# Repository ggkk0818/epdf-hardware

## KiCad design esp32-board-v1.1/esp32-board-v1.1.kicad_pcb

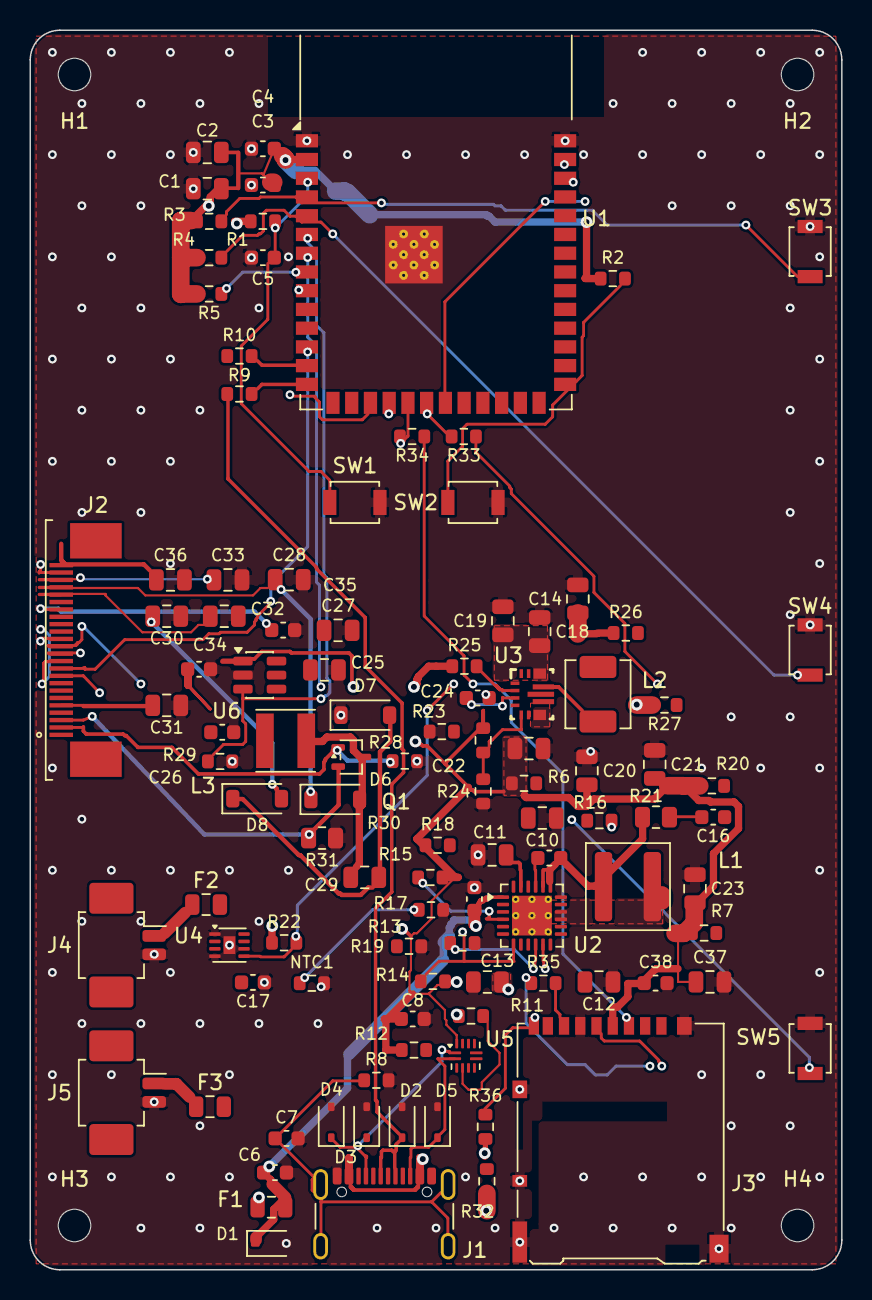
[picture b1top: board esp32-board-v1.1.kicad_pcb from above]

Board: 4 copper layers, 55.0 x 84.0 mm, 110 parts (0 on the bottom side), 70 nets.

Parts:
C1, C2, C10, C12, C13, C14, C15, C18, C19, C20, C21, C22, C23, C25, C27, C28, C29, C30, C31, C32, C33, C36, C37: C_0805_2012Metric
C3, C4, C5, C6, C7, C8, C9, C11, C16, C17, C24, C26, C34, C35, C38: C_0603_1608Metric
D1, D2, D3, D4, D5: D_SOD-323
D6, D7, D8: D_SOD-123
F1, F2, F3: Fuse_0805_2012Metric
H1, H2, H3, H4: MountingHole_2.2mm_M2
J1: USB_C_Receptacle_GCT_USB4105-xx-A_16P_TopMnt_Hori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; USB_C_Receptacle_GCT_USB4105-xx-A_16P_TopMnt_Horizontal
J2: X05B20U24T
J3: microSD_DM3AT-SF-PEJM5_EPDF
J4, J5: Molex_PicoBlade_53261-0271_1x02-1MP_P1.25mm_Horiz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; Molex_PicoBlade_53261-0271_1x02-1MP_P1.25mm_Horizontal
L1: L_Coilcraft_XAL5030-XXX
L2: L_Sunlord_MWSA0402S
L3: L_Taiyo-Yuden_NR-40xx
NTC1: R_0603_1608Metric
Q1: SOT-323_SC-70
R1, R2, R3, R4, R5, R6, R7, R8, R9, R10, R11, R12, R13, R14, R15, R16, R17, R18, R19, R20, R22, R23, R24, R25, R26, R27, R28, R29, R30, R32, R33, R34, R35, R36: R_0603_1608Metric
R21, R31: R_0805_2012Metric
SW1, SW2, SW3, SW4, SW5: SW_SPST_B3U-1000P
U1: ESP32-S3-WROOM-1_EPDF
U2: Texas_RTW_WQFN-24-1EP_4x4mm_P0.5mm_EP2.7x2.7mm_Th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; Texas_RTW_WQFN-24-1EP_4x4mm_P0.5mm_EP2.7x2.7mm_ThermalVias
U3: RNM0015A
U4: TDFN-8-1EP_2x2mm_P0.5mm_EP0.8x1.2mm
U5: Texas_X2QFN-12_1.6x1.6mm_P0.4mm
U6: SOT-23-6

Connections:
3V3_MAIN: C1.1, C2.1, C3.1, C4.1, C8.1, C20.1, C21.1, C22.1, C23.1, C37.1, C38.1, J3.4, R1.1, R2.1, R3.1, R4.1, R5.1, R6.1, R7.1, R12.1, R14.2, R15.2, R18.1, R20.1, R22.1, R23.1, R25.1, R32.1, R36.1, U1.2, U3.7, U3.8, U5.12, U6.1
BAT1_RAW: F2.1, J4.1
BAT2_RAW: F3.1, J5.1
BAT_BUS: C12.1, C17.1, F2.2, F3.2, U2.13, U2.14, U4.2, U4.3
BOOT: R2.2, SW2.1, U1.27
CHG_BTST: C11.1, U2.21
CHG_CE: R18.2, U1.24, U2.9
CHG_DSEL: R20.2, U2.24
CHG_ILIM: R13.1, U2.10
CHG_INT_N: R14.1, U1.9, U2.7
CHG_OTG: R19.1, U2.8
CHG_PMID: C15.1, U2.23
CHG_REGN: C10.1, R16.1, U2.22
CHG_SNUB: C16.1, R21.2
CHG_STAT: R15.1, U2.4
CHG_SW: C11.2, L1.1, R21.1, U2.19, U2.20
CHG_TS: NTC1.1, R16.2, R17.1, U2.11
EPD_3V3: C25.1, C26.1, C27.1, C34.1, J2.15, J2.16, L3.1, U6.6
EPD_BUSY: J2.9, U1.7
EPD_CS_N: J2.12, U1.18
EPD_DC: J2.11, U1.17
EPD_GDR: J2.2, Q1.1, R30.1
EPD_PWR_EN: R29.1, U1.6, U6.3
EPD_RESE: J2.3, Q1.2, R31.1
EPD_RST_N: J2.10, U1.12
EPD_SW: C29.1, D6.2, L3.2, Q1.3
EPD_VCOM: C36.1, J2.24
EPD_VDD: C35.1, J2.18
EPD_VGH: C28.1, D6.1, J2.21
EPD_VGL: C30.1, D8.2, J2.23
EPD_VSH1: C32.1, J2.20
EPD_VSH2: C31.1, J2.5
EPD_VSL: C33.1, J2.22
EPD_X: C29.2, D7.2, D8.1
FG_ALRT_N: R22.2, U1.39, U4.5
GND: C1.2, C2.2, C3.2, C4.2, C5.2, C6.2, C7.2, C8.2, C9.2, C10.2, C12.2, C13.2, C14.2, C15.2, C16.2, C17.2, C18.2, C19.2, C20.2, C21.2, C22.2, C23.2, C24.2, C25.2, C26.2, C27.2, C28.2, C30.2, C31.2, C32.2, C33.2, C34.2, C35.2, C36.2, C37.2, C38.2, D1.2, D2.2, D3.2, D4.2, D5.2, D7.1, J1.A1, J1.A12, J1.B1, J1.B12, J2.8, J2.17, J3.6, J3.10, J3.SH, J4.2, J5.2, NTC1.2, R8.2, R13.2, R17.2, R19.2, R24.2, R28.1, R29.2, R30.2, R31.2, SW1.2, SW2.2, SW3.2, SW4.2, SW5.2, U1.1, U1.40, U1.41, U2.17, U2.18, U2.25, U3.4, U3.10, U4.1, U4.4, U4.6, U4.9, U5.3, U5.5, U5.10, U5.11, U6.2
I2C_SCL: R7.2, U1.23, U2.5, U4.7, U5.8
I2C_SDA: R6.2, U1.11, U2.6, U4.8, U5.7
KEY1_N: R3.2, SW3.1, U1.4
KEY2_N: R4.2, SW4.1, U1.5
KEY3_N: R5.2, SW5.1, U1.8
RESET_N: C5.1, R1.2, SW1.1, U1.3
SPI_MISO: R35.1, U1.21
SPI_MOSI: J2.14, R34.1, U1.19
SPI_SCLK: J2.13, R33.1, U1.20
SYS: C13.1, C14.1, C18.1, C19.1, L1.2, R26.1, R27.1, U2.15, U2.16, U3.12, U3.13
TF_CD_N: J3.9, R36.2, U1.38
TF_CS_N: J3.2, R32.2, U1.22
TF_MISO: J3.7, R35.2
TF_MOSI: J3.3, R34.2
TF_SCLK: J3.5, R33.2
TPS_EN: R26.2, U3.14
TPS_FB: R23.2, R24.1, U3.5
TPS_L1: L2.1, U3.11
TPS_L2: L2.2, U3.9
TPS_PG: R25.2, U3.2
TPS_PS_SYNC: R27.2, U3.1
TPS_VAUX: C24.1, U3.3
TPS_VSEL: R28.2, U3.15
TYPEC_INT_N: R12.2, U1.10, U5.6
USB_CC1: D4.1, J1.A5, U5.1
USB_CC2: D5.1, J1.B5, U5.2
USB_DN: R10.2, U1.13
USB_DN_CONN: D3.1, J1.A7, J1.B7, R10.1
USB_DP: R9.2, U1.14
USB_DP_CONN: D2.1, J1.A6, J1.B6, R9.1
USB_SHIELD: C7.1, J1.SH, R8.1
USB_VBUS_DET: R11.2, U5.4
USB_VBUS_PROT: C6.1, C9.1, D1.1, F1.2, U2.1
USB_VBUS_RAW: F1.1, J1.A4, J1.A9, J1.B4, J1.B9, R11.1

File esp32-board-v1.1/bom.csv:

"Reference","Value","Footprint","Status","MPN","Populate"
"C1,C13,C14,C21-C23","22uF","Capacitor_SMD:C_0805_2012Metric","RELEASED","TCC0805X5R226K250FT（华秋 G14559843）","FIT"
"C2,C12,C15,C18-C20,C25,C37","10uF","Capacitor_SMD:C_0805_2012Metric","RELEASED","CL21A106KAYNNNE（华秋 G0022684）","FIT"
"C3,C5,C6,C9","1uF","Capacitor_SMD:C_0603_1608Metric","RELEASED","","FIT"
"C4,C8,C17,C26,C38","0.1uF","Capacitor_SMD:C_0603_1608Metric","RELEASED","","FIT"
"C7","1nF","Capacitor_SMD:C_0603_1608Metric","RELEASED","","FIT"
"C10","4.7uF/10V","Capacitor_SMD:C_0805_2012Metric","RELEASED","","FIT"
"C11","47nF","Capacitor_SMD:C_0603_1608Metric","RELEASED","","FIT"
"C16","470pF","Capacitor_SMD:C_0603_1608Metric","RELEASED","","DNP"
"C24","100nF","Capacitor_SMD:C_0603_1608Metric","RELEASED","","FIT"
"C27-C33","4.7uF/25V","Capacitor_SMD:C_0805_2012Metric","RELEASED","CL21A475KAQNNNG（华秋 G0936665）","FIT"
"C34,C35","1uF/25V","Capacitor_SMD:C_0603_1608Metric","RELEASED","CL10B105KA8NNNC（华秋 G0021698）","FIT"
"C36","1uF/25V","Capacitor_SMD:C_0805_2012Metric","RELEASED","0805B105K250AT（华秋 G4185910）","FIT"
"D1","TVS 5.6V","Diode_SMD:D_SOD-323","RELEASED","PESD5V0S1BA,115（华秋 G0089294）","FIT"
"D2,D3","ESD","Diode_SMD:D_SOD-323","RELEASED","GBLC05C（华秋 G5954860）","FIT"
"D4,D5","ESD","Diode_SMD:D_SOD-323","RELEASED","LESD3Z5.0CMT1G（华秋 G4193578）","FIT"
"D6-D8","MBR0530","Diode_SMD:D_SOD-123","RELEASED","MBR0530T1G（华秋 G3325533）","FIT"
"F1-F3","2A PTC","Fuse:Fuse_0805_2012Metric","RELEASED","BSMD0805L-200（华秋 G5053245）","FIT"
"J1","USB-C 2.0 Sink","Connector_USB:USB_C_Receptacle_GCT_USB4105-xx-A_16P_TopMnt_Horizontal","RELEASED","GCT USB4105-15-A-120","FIT"
"J2","GDEM102T91 24P FPC","esp32-board-v1.1:X05B20U24T","RELEASED","XKB X05B20U24T","FIT"
"J3","MicroSD","esp32-board-v1.1:microSD_DM3AT-SF-PEJM5_EPDF","RELEASED","Hirose DM3AT-SF-PEJM5","FIT"
"J4","BAT1","Connector_Molex:Molex_PicoBlade_53261-0271_1x02-1MP_P1.25mm_Horizontal","RELEASED","Molex 53261-0271","FIT"
"J5","BAT2","Connector_Molex:Molex_PicoBlade_53261-0271_1x02-1MP_P1.25mm_Horizontal","RELEASED","Molex 53261-0271","FIT"
"L1","1.0uH","Inductor_SMD:L_Sunlord_MWSA0503S","RELEASED","Sunlord MWSA0503S-1R0MT（华秋 G4719678）","FIT"
"L2","1.2uH","Inductor_SMD:L_Sunlord_MWSA0402S","RELEASED","Sunlord MWSA0402S-1R2MT","FIT"
"L3","47uH","Inductor_SMD:L_Changjiang_FNR4020S","RELEASED","cjiang FHD4020S-470MT（华秋 G6635066）","FIT"
"NTC1","10k B3435","Resistor_SMD:R_0603_1608Metric","RELEASED","Vishay NTCS0603E3103FLT","FIT"
"Q1","Si1304BDL","Package_TO_SOT_SMD:SOT-323_SC-70","RELEASED","Si1304BDL-T1-GE3","FIT"
"R1-R5,R12,R14,R15,R18,R20,R22,R25,R26,R32,R36","10k","Resistor_SMD:R_0603_1608Metric","RELEASED","","FIT"
"R6,R7","4.7k","Resistor_SMD:R_0603_1608Metric","RELEASED","","FIT"
"R8,R33-R35","0","Resistor_SMD:R_0603_1608Metric","RELEASED","","FIT"
"R9,R10","22","Resistor_SMD:R_0603_1608Metric","RELEASED","","FIT"
"R11","900k","Resistor_SMD:R_0603_1608Metric","RELEASED","","FIT"
"R13","180","Resistor_SMD:R_0603_1608Metric","RELEASED","0603WAF1800T5E（华秋 G3705022）","FIT"
"R16","5.23k","Resistor_SMD:R_0603_1608Metric","RELEASED","0603WAF5231T5E（华秋 G3705144）","FIT"
"R17","30.1k","Resistor_SMD:R_0603_1608Metric","RELEASED","RC0603DR-0730K1L（华秋 G4243913）","FIT"
"R19,R27-R29","100k","Resistor_SMD:R_0603_1608Metric","RELEASED","","FIT"
"R21","2.2","Resistor_SMD:R_0805_2012Metric","RELEASED","","DNP"
"R23","470k","Resistor_SMD:R_0603_1608Metric","RELEASED","0603WAF4703T5E（华秋 G0064373）","FIT"
"R24","150k","Resistor_SMD:R_0603_1608Metric","RELEASED","RC0603FR-07150KL（华秋 G0072618）","FIT"
"R30","1M","Resistor_SMD:R_0603_1608Metric","RELEASED","","FIT"
"R31","2.2","Resistor_SMD:R_0805_2012Metric","RELEASED","","FIT"
"SW1","RESET","Button_Switch_SMD:SW_SPST_B3U-1000P","RELEASED","Omron B3U-1000P","FIT"
"SW2","BOOT","Button_Switch_SMD:SW_SPST_B3U-1000P","RELEASED","Omron B3U-1000P","FIT"
"SW3","KEY1","Button_Switch_SMD:SW_SPST_B3U-1000P","RELEASED","Omron B3U-1000P","FIT"
"SW4","KEY2","Button_Switch_SMD:SW_SPST_B3U-1000P","RELEASED","Omron B3U-1000P","FIT"
"SW5","KEY3","Button_Switch_SMD:SW_SPST_B3U-1000P","RELEASED","Omron B3U-1000P","FIT"
"U1","ESP32-S3-WROOM-1-N16R8","esp32-board-v1.1:ESP32-S3-WROOM-1_EPDF","RELEASED","ESP32-S3-WROOM-1-N16R8","FIT"
"U2","BQ25895RTW","Package_DFN_QFN:Texas_RTW_WQFN-24-1EP_4x4mm_P0.5mm_EP2.7x2.7mm_ThermalVias","RELEASED","BQ25895RTWT","FIT"
"U3","TPS63070RNMT","esp32-board-v1.1:RNM0015A","RELEASED","TPS63070RNMT","FIT"
"U4","MAX17048","Package_DFN_QFN:TDFN-8-1EP_2x2mm_P0.5mm_EP0.8x1.2mm","RELEASED","MAX17048G+T10","FIT"
"U5","TUSB320LI","Package_DFN_QFN:Texas_X2QFN-12_1.6x1.6mm_P0.4mm","RELEASED","TUSB320LIRWBR","FIT"
"U6","TPS22918","Package_TO_SOT_SMD:SOT-23-6","RELEASED","TPS22918","FIT"

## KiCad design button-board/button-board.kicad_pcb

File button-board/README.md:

# button-board

这是一个面向华秋 KiCad（KiCad 10 兼容）的按键板原理图工程。

原理图 `button-board.kicad_sch` 已包含：

- 3 个贴片轻触开关 `TS3315A`：`SW1=UP`、`SW2=DWN`、`SW3=ENT`，开关公共端共地。
- 1 个 SH1.0 4P 卧贴母座 `WAFER-SH1.0-4PWB`，引脚顺序为 `1=UP`、`2=DWN`、`3=ENT`、`4=G`。
- 信号网络标签：`UP`、`DWN`、`ENT`、`G`。

PCB `button-board.kicad_pcb` 已包含：

- 板框 12 x 114 mm，四角圆角 R2，板厚 1.2 mm，2 层板。
- 三个 `TS3315A` 贴片轻触开关中心：`SW1=(6,30)`、`SW2=(6,84)`、`SW3=(6,57)`。
- 两个定位孔：`(6,4)`、`(6,110)`，直径 2.2 mm，NPTH。
- `WAFER-SH1.0-4PWB` 卧贴母座 `J1` 位于 `(2,100)`，接线方向朝右（+x，相对原方向顺时针旋转 180°）。
- 连接器丝印线序（从上到下）：`4 G`、`3 ENT`、`2 DWN`、`1 UP`。

## 器件

- 轻触开关：TS3315A，`button-board:TS3315A`，华秋器件库链接：https://item.hqchip.com/2500431492.html
- SH1.0 母座：WAFER-SH1.0-4PWB，`button-board:WAFER-SH1.0-4PWB`，华秋器件库链接：https://item.hqchip.com/2500435391.html

## 打开方式

1. 启动华秋 KiCad。
2. 选择“打开工程”，打开本目录下的 `button-board.kicad_pro`。
3. 在工程管理器中分别打开 `button-board.kicad_sch` 和 `button-board.kicad_pcb`。
4. 如果华秋 KiCad 此前已经打开该原理图或 PCB，请先关闭并重新打开对应文件，以加载本文件的最新内容。

## 华秋器件库

华秋器件库通过华秋 KiCad 内置的“华秋库面板 / Component Search”提供，工程内不需要保存云端账号信息。打开原理图后，可在工具栏中打开华秋器件搜索面板，搜索型号、参数或描述，然后将器件直接摆放到原理图中。

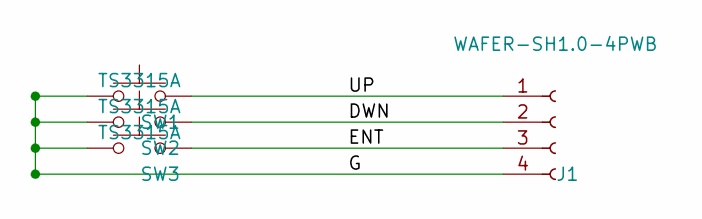
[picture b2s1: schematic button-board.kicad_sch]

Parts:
J1: WAFER-SH1.0-4PWB
SW1, SW2, SW3: TS3315A

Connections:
DWN: J1.2, SW2.2
ENT: J1.3, SW3.2
G: J1.4, SW1.1, SW2.1, SW3.1
UP: J1.1, SW1.2

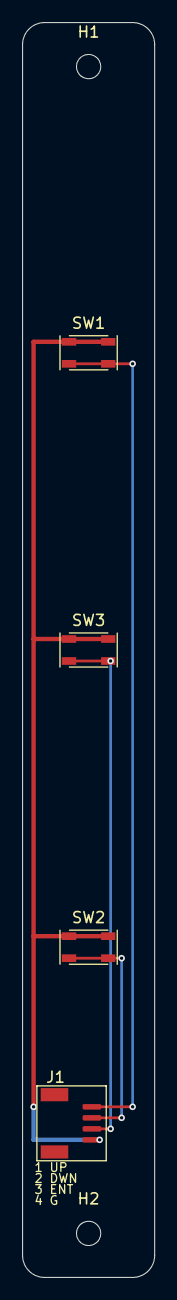
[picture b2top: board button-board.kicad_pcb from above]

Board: 2 copper layers, 12.0 x 114.0 mm, 6 parts (0 on the bottom side), 4 nets.

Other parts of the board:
H1, H2: MountingHole_2.2mm_M2

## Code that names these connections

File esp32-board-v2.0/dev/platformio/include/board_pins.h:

// =====================================================================
//  ESP32-S3 墨水屏主板 v2.0 - 板级引脚与器件定义
//  来源：EasyEDA 工程 esp32s3-board-v2.0 原理图 P1/P2 网表现场回读
//  生成日期：2026-10-10   原理图版本：V1.0（更新 2026-10-07）
//  详见 ../PINOUT.md / ../I2C_DEVICES.md / ../POWER_AND_CHARGING.md
// =====================================================================
#pragma once

#include <Arduino.h>

// ------------------------- 主控与电源 --------------------------------
#define BOARD_NAME          "ESP32-S3-EPD-102-V2.0"
#define MCU_MODULE          "ESP32-S3-WROOM-1-N16R8"

// ------------------------- 用户按键（低有效）-------------------------
#define PIN_KEY1            4    // SW3  右侧按键 1   (KEY1_N)
#define PIN_KEY2            5    // SW4  右侧按键 2   (KEY2_N)
#define PIN_KEY3            15   // SW5  右侧按键 3   (KEY3_N)
#define PIN_BOOT            0    // SW2  BOOT / 下载

// ------------------------- 墨水屏（SSD1677 / 24P FPC）----------------
#define PIN_EPD_PWR_EN      6    // 高=给面板上电（TPS22918），默认下拉=断电
#define PIN_EPD_BUSY        7    // 高=忙（面板输出）
#define PIN_EPD_RST         8    // 复位，低有效
#define PIN_EPD_DC          9    // 1=数据 0=命令
#define PIN_EPD_CS          10   // 片选，低有效

// ------------------------- SPI（墨水屏 + microSD 共用）---------------
#define PIN_SPI_SCK         12
#define PIN_SPI_MOSI        11
#define PIN_SPI_MISO        13   // 只有 microSD 在用（面板无 MISO）
#define PIN_SD_CS           14   // microSD 片选，低有效
#define PIN_SD_CD           2    // microSD 卡检测：插卡=低

// ------------------------- I2C ---------------------------------------
#define PIN_I2C_SDA         18
#define PIN_I2C_SCL         21
#define I2C_FREQ_HZ         400000UL   // 调试阶段建议 100000

// ------------------------- 中断 / 控制 -------------------------------
#define PIN_CHG_INT         16   // BQ25895 /INT      低有效（开漏）
#define PIN_TYPEC_INT       17   // TUSB320 INT_N     低有效（开漏）
#define PIN_FG_ALRT         1    // MAX17048 ALRT     低有效（开漏）
#define PIN_CHG_CE          47   // BQ25895 /CE：低=允许充电（上电默认高=禁止）
#define PIN_LED_DIN         38   // WS2812 数据（经 R37 33Ω）

// ------------------------- I2C 从机地址（7 位）-----------------------
#define ADDR_BQ25895        0x6A   // 充电器
#define ADDR_MAX17048       0x36   // 电量计
#define ADDR_TUSB320        0x47   // Type-C 控制器（ADDR 脚接 GND）

// ------------------------- BQ25895 寄存器 ----------------------------
#define BQ_REG_INPUT_LIMIT  0x00   // EN_HIZ / EN_ILIM / IINLIM[5:0]
#define BQ_REG_THERM_VINDPM 0x01
#define BQ_REG_ADC_CTRL     0x02
#define BQ_REG_MODE_CFG     0x03   // bit5 OTG_CONFIG(1=升压) / bit4 CHG_CONFIG(1=允许充电) / bit3:1 SYS_MIN
// 注意：CHG_CONFIG 在 bit4，关 OTG 且开充电应写 0x1A；写成 0x2A 会变成“开 OTG、关充电”
#define BQ_MODE_CFG_OTG_OFF_CHG_ON  0x1A
#define BQ_REG_ICHG         0x04   // 充电电流，64 mA/LSB
#define BQ_REG_ITERM_IPRE   0x05   // 终止/预充电流，64 mA/LSB + 64 mA
#define BQ_REG_VREG         0x06   // 充电电压，16 mV/LSB + 3.840 V
#define BQ_REG_TERM_TIMER   0x07   // EN_TERM / WATCHDOG / CHG_TIMER
#define BQ_REG_STATUS       0x0B   // 只读状态
#define BQ_REG_FAULT        0x0C   // 只读故障（需连读两次）

#define BQ_STATUS_CHRG_MASK 0x18   // CHRG_STAT[1:0] = bit4:3
#define BQ_STATUS_CHRG_SHIFT 3
#define BQ_STATUS_PG        0x04   // PG_STAT = bit2

// ------------------------- MAX17048 寄存器 ---------------------------
#define MAX_REG_VCELL       0x02   // ×78.125 µV
#define MAX_REG_SOC         0x04   // ÷256 = %
#define MAX_REG_MODE        0x06
#define MAX_REG_CONFIG      0x0C   // bit5 ALRT（写 0 清报警）
#define MAX_REG_CRATE       0x16   // 有符号，0.208 %/h LSB（正=充电 负=放电）
#define MAX_REG_STATUS      0x1A
#define MAX_REG_CMD         0xFE   // 写 0x5400 = POR

// ------------------------- TUSB320 寄存器 ----------------------------
#define TYPEC_REG_DEVICE_ID 0x00   // 0x06..0x00 = "TUSB320"（反向读取）
#define TYPEC_REG_CURRENT   0x08   // CURRENT_MODE_ADVERTISE / _DETECT
#define TYPEC_REG_ATTACH    0x09   // ATTACHED_STATE / INTERRUPT_STATUS(bit4,写1清)
#define TYPEC_REG_MODE      0x0A   // MODE_SELECT / DISABLE_TERM
